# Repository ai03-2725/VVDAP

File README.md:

# VVDAP
Variable voltage isolated DAPLink programmer  

**Warning:** Currently untested.  
If testing, proceed at your own risk.  

## Features
- DAPLink capabilities
  - [DAPLink](https://daplink.io) programming device for flashing Arm Cortex devices
  - Standard 10-pin (5x2) 1.27mm pitch Cortex debug connector for connection to target
  - Exposes UART pins - for future variable-voltage UART module addon via spring-loaded headers
- Variable voltage
  - Variable I/O voltage from 1.8 to 3.6V which self-adjusts to match the target VCC voltage provided on Vtref pin of debug header
- Protection
  - Full isolation between host and target to avoid ground loops or damage to host
  - ESD protection on USB lines and debug connector I/O
  - Polyfuse on USB VBUS
- Modern nice-to-haves
  - USB-C 
  - Fairly compact single-board solution
  - Relatively straightforward to solder at home with a reflow plate and (possibly 3D-printed) solder paste stencil
  - Very affordable (likely <15 USD) compared to the multi-hundred dollar commercial programmers

## Credits
This project builds upon the shoulders of giants - credits go to the following for nearly all of the heavy lifting.  
- [XIVN1987's DAPLink port](https://github.com/XIVN1987/DAPLink) to the CH32V203 microcontroller
- [XIVN1987's reference CH32V203/AT32F425 hardware design](https://oshwhub.com/xivn1987/daplink) for the above port
- [盐汽水-BD4USQ's DAPLink isolator design](https://oshwhub.com/yanqisui/dap-jlink-ge-li-diao-shi-kuo-zhan-ka) (and in turn the projects which it credits) which makes push-pull SWDIO possible over unidirectional isolators/transcievers 

## Changes from the above
- Swapped the digital I/O isolator to an ADuM162N capable of reaching low I/O voltage levels
- Added ESD protection on USB and I/O lines using TPD4E05U06 and ESD5Z5V0 TVS diodes
- Isolated voltage supply rail using the MIE1W0505/R05C1TF05S compact isolated DC/DC converter
- Added a TPS7B4250 tracking LDO to replicate the voltage provided on the Vtref pin of the debug header from the isolated supply rail, which in turn powers the secondary side of the I/O isolator and push-pull splitter
- Changed output connector to a 10-pin (2x5) 1.27mm pitch Cortex debug header
- Removed all power output capabilities 
  - Target should self-power to avoid potentially dangerous voltage mismatches, reverse voltage injection into circuitry not designed to withstand it, or voltage injection into batteries
- Misc component swaps

## Todo
- Produce and test
- Make a 3D printed case
- Make a variable voltage UART module which stacks onto the main board

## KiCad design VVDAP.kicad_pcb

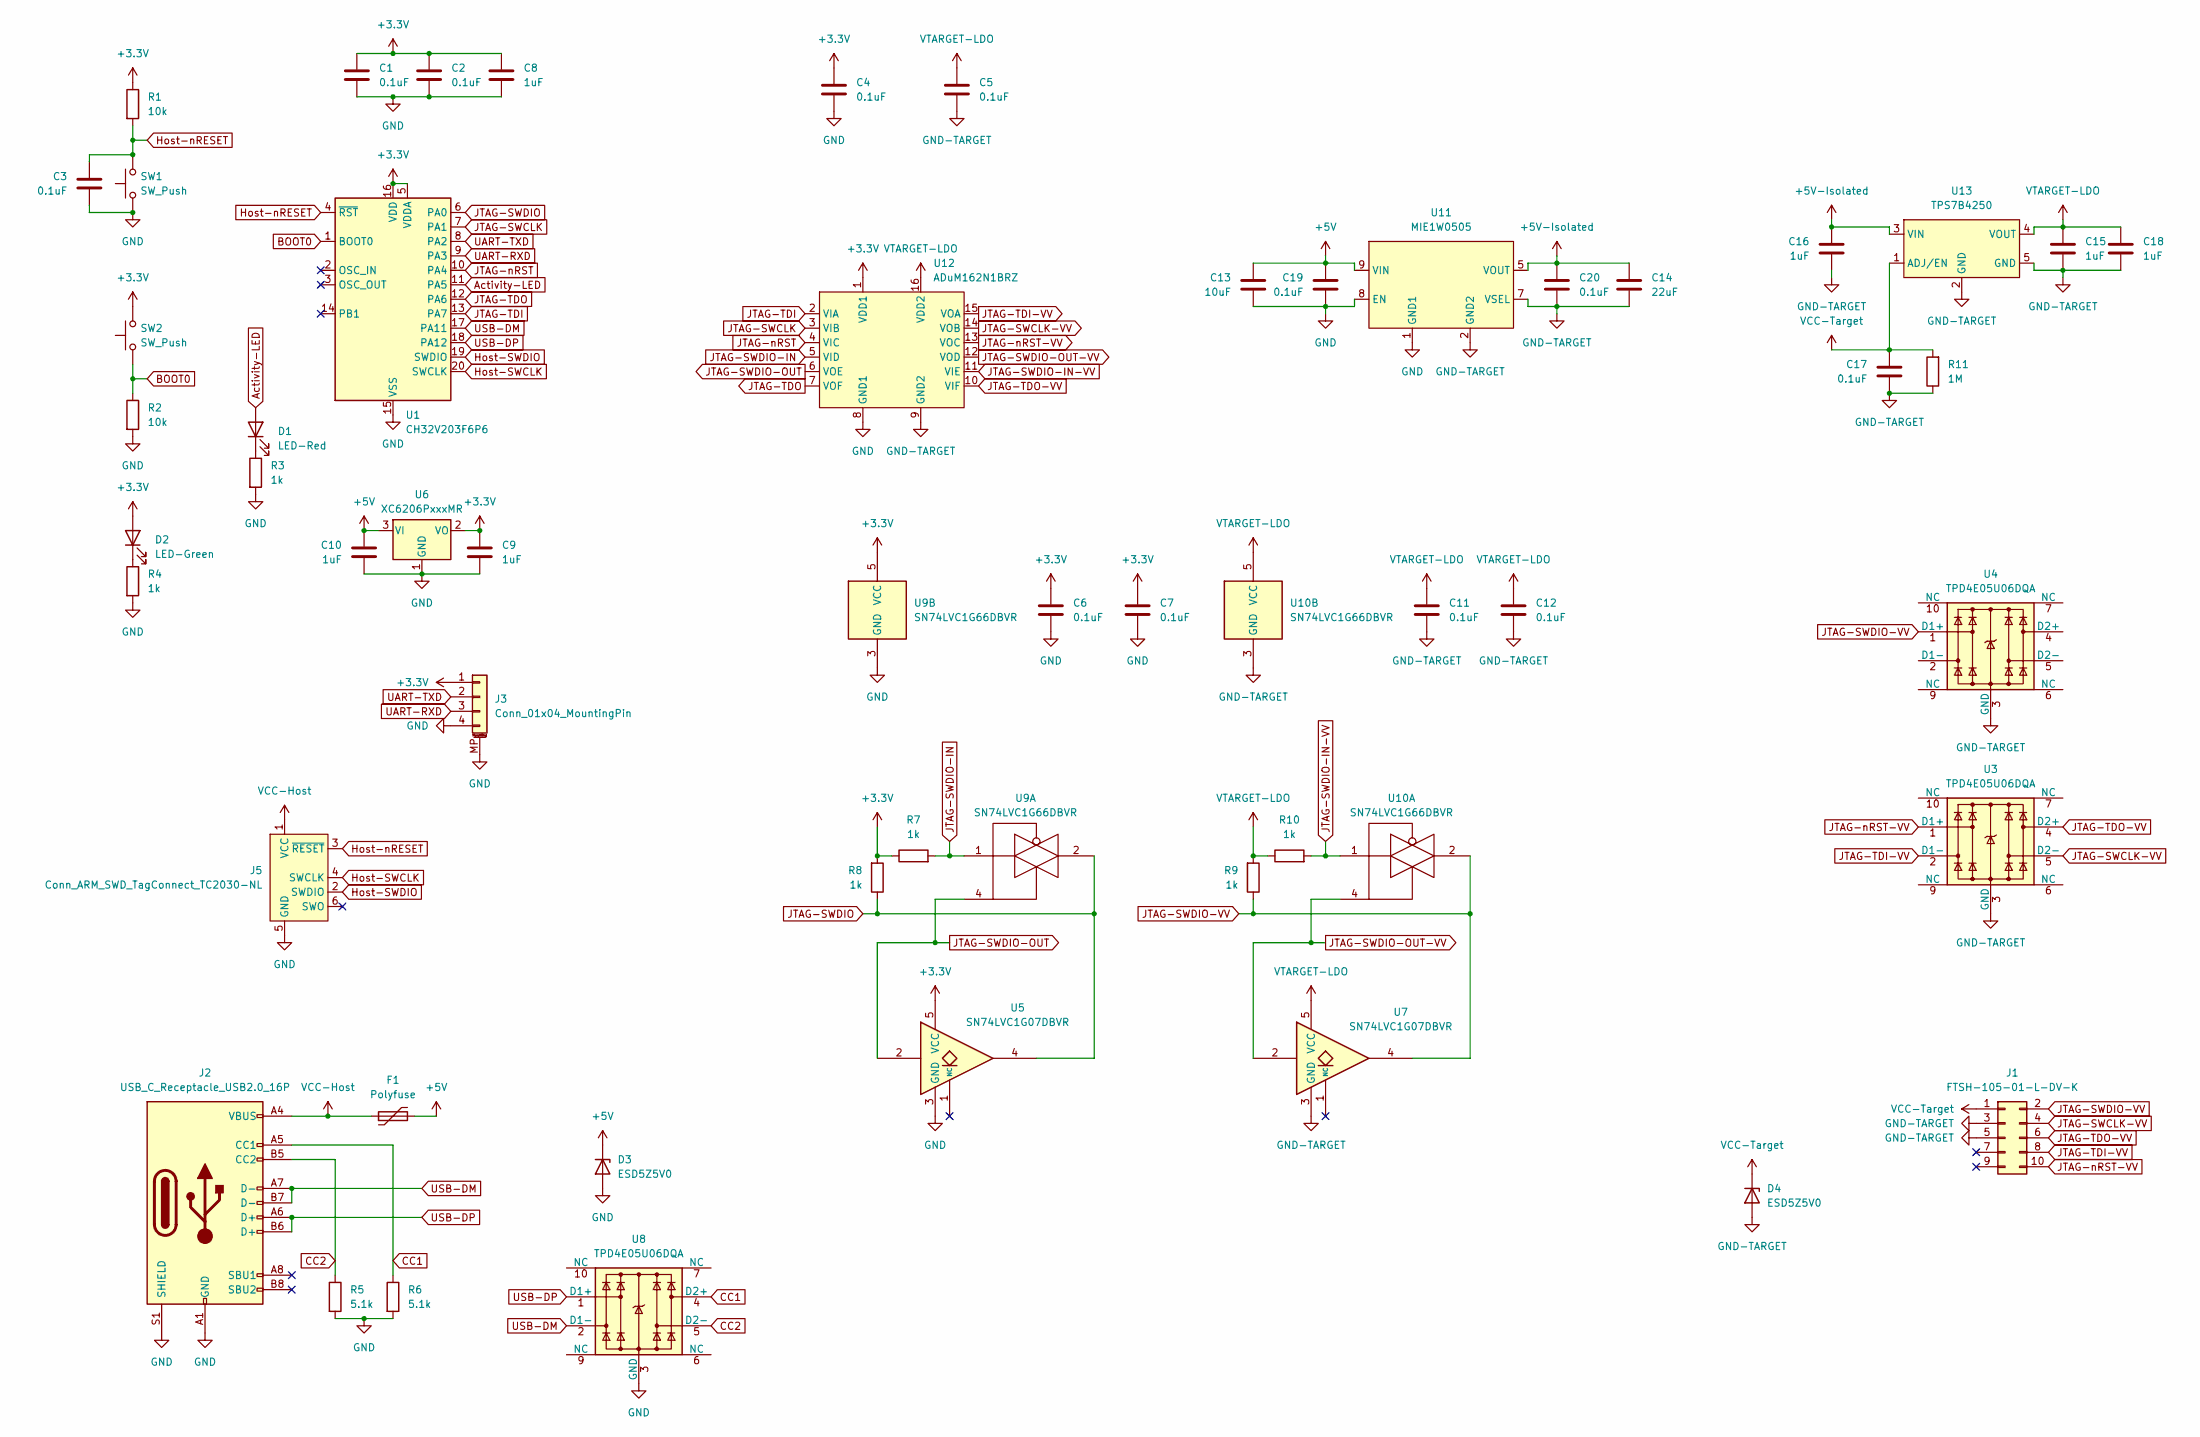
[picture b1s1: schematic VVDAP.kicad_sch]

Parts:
C1, C2, C3, C4, C5, C6, C7, C11, C12, C17, C19, C20: 0.1uF; C_0603_1608Metric
C8, C9, C10, C15, C16, C18: 1uF; C_0603_1608Metric
C13: 10uF; C_0603_1608Metric
C14: 22uF; C_1206_3216Metric
D1: LED-Red; LED_0603_1608Metric
D2: LED-Green; LED_0603_1608Metric
D3, D4: ESD5Z5V0; D_SOD-523
F1: Polyfuse; Fuse_1206_3216Metric
J1: FTSH-105-01-L-DV-K
J2: USB_C_Receptacle_USB2.0_16P; USB_C_Receptacle_HRO_TYPE-C-31-M-12
J3: Conn_01x04_MountingPin; PogoReceiver-2.54-4
J5: Conn_ARM_SWD_TagConnect_TC2030-NL; Tag-Connect_TC2030-IDC-NL_2x03_P1.27mm_Vertical
R1, R2: 10k; R_0603_1608Metric
R3, R4, R7, R8, R9, R10: 1k; R_0603_1608Metric
R5, R6: 5.1k; R_0603_1608Metric
R11: 1M; R_0603_1608Metric
SW1, SW2: SW_Push; SW_SPST_TS-1088-xR020
U1: CH32V203F6P6; TSSOP-20_4.4x6.5mm_P0.65mm
U3, U4, U8: TPD4E05U06DQA; USON-10_2.5x1.0mm_P0.5mm
U5, U7: SN74LVC1G07DBVR; SOT-23-5
U6: XC6206PxxxMR; SOT-23-3
U9, U10: SN74LVC1G66DBVR; SOT-23-5
U11: MIE1W0505
U12: ADuM162N1BRZ; SOIC-16_3.9x9.9mm_P1.27mm
U13: TPS7B4250; SOT-23-5

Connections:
+3.3V: C1.1, C2.1, C4.1, C6.1, C7.1, C8.1, C9.1, D2.2 (A), J3.1, R1.1, R7.1, R8.2, SW2.2, U1.5 (VDDA), U1.16 (VDD), U5.5 (VCC), U6.2 (VO), U9.5 (VCC), U12.1 (VDD1)
+5V: C10.1, C13.1, C19.1, D3.1 (K), F1.2, U6.3 (VI), U11.9 (VIN), U11.10 (VIN)
+5V-Isolated: C14.1, C16.1, C20.1, U11.5 (VOUT), U11.6 (VOUT), U13.3 (VIN)
Activity-LED: D1.2 (A), U1.11 (PA5)
BOOT0: R2.1, SW2.1, U1.1 (BOOT0)
CC1: J2.A5 (CC1), R6.1, U8.4 (D2+)
CC2: J2.B5 (CC2), R5.1, U8.5 (D2-)
GND: C1.2, C2.2, C3.2, C4.2, C6.2, C7.2, C8.2, C9.2, C10.2, C13.2, C19.2, D3.2 (A), J2.A1 (GND), J2.A12 (GND), J2.B1 (GND), J2.B12 (GND), J2.S1 (SHIELD), J3.4, J3.MP (MountPin), J5.5 (GND), R2.2, R3.2, R4.2, R5.2, R6.2, SW1.1, U1.15 (VSS), U5.3 (GND), U6.1 (GND), U8.3 (GND), U8.8 (GND), U9.3 (GND), U11.1 (GND1), U11.8 (EN), U11.11 (GND1), U11.12 (GND1), U12.8 (GND1)
GND-TARGET: C5.2, C11.2, C12.2, C14.2, C15.2, C16.2, C17.2, C18.2, C20.2, D4.2 (A), J1.3, J1.5, R11.1, U3.3 (GND), U3.8 (GND), U4.3 (GND), U4.8 (GND), U7.3 (GND), U10.3 (GND), U11.2 (GND2), U11.3 (GND2), U11.4 (GND2), U11.7 (VSEL), U12.9 (GND2), U13.2 (GND), U13.5 (GND)
Host-SWCLK: J5.4 (SWCLK), U1.20 (SWCLK)
Host-SWDIO: J5.2 (SWDIO), U1.19 (SWDIO)
Host-nRESET: C3.1, J5.3 (~RESET), R1.2, SW1.2, U1.4 (~RST)
JTAG-SWCLK: U1.7 (PA1), U12.3 (VIB)
JTAG-SWCLK-VV: J1.4, U3.5 (D2-), U12.14 (VOB)
JTAG-SWDIO: R8.1, U1.6 (PA0), U5.4, U9.2
JTAG-SWDIO-IN: R7.2, U9.1, U12.5 (VID)
JTAG-SWDIO-IN-VV: R10.2, U10.1, U12.11 (VIE)
JTAG-SWDIO-OUT: U5.2, U9.4, U12.6 (VOE)
JTAG-SWDIO-OUT-VV: U7.2, U10.4, U12.12 (VOD)
JTAG-SWDIO-VV: J1.2, R9.1, U4.1 (D1+), U7.4, U10.2
JTAG-TDI: U1.13 (PA7), U12.2 (VIA)
JTAG-TDI-VV: J1.8, U3.2 (D1-), U12.15 (VOA)
JTAG-TDO: U1.12 (PA6), U12.7 (VOF)
JTAG-TDO-VV: J1.6, U3.4 (D2+), U12.10 (VIF)
JTAG-nRST: U1.10 (PA4), U12.4 (VIC)
JTAG-nRST-VV: J1.10, U3.1 (D1+), U12.13 (VOC)
unnamed: D1.1 (K), R3.1
unnamed: D2.1 (K), R4.1
UART-RXD: J3.3, U1.9 (PA3)
UART-TXD: J3.2, U1.8 (PA2)
USB-DM: J2.A7 (D-), J2.B7 (D-), U1.17 (PA11), U8.2 (D1-)
USB-DP: J2.A6 (D+), J2.B6 (D+), U1.18 (PA12), U8.1 (D1+)
VCC-Host: F1.1, J2.A4 (VBUS), J2.A9 (VBUS), J2.B4 (VBUS), J2.B9 (VBUS), J5.1 (VCC)
VCC-Target: C17.1, D4.1 (K), J1.1, R11.2, U13.1 (ADJ/EN)
VTARGET-LDO: C5.1, C11.1, C12.1, C15.1, C18.1, R9.2, R10.1, U7.5 (VCC), U10.5 (VCC), U12.16 (VDD2), U13.4 (VOUT)

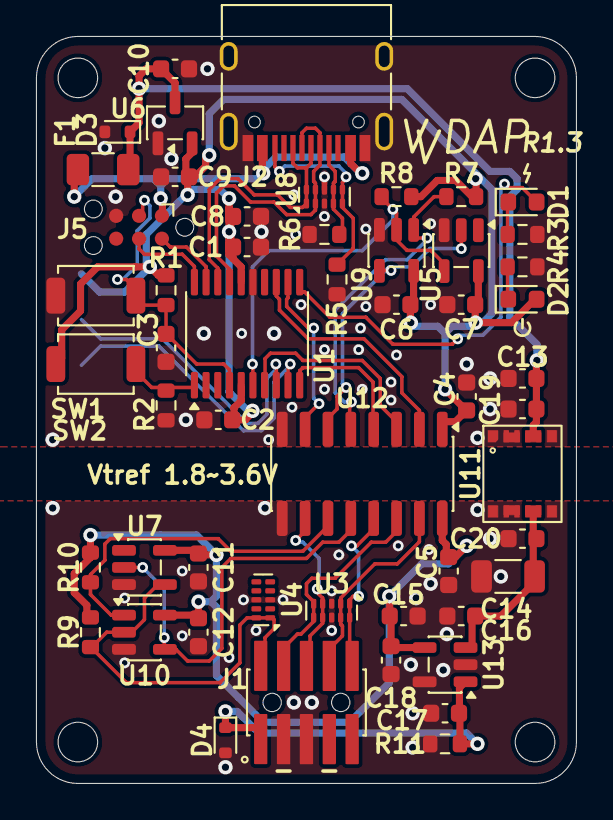
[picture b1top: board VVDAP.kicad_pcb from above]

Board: 2 copper layers, 30.0 x 41.5 mm, 54 parts (1 on the bottom side), 35 nets.

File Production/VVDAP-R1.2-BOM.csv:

Reference,Qty,Value,DNP,Footprint,Description
"C1,C2,C3,C4,C5,C6,C7,C11,C12,C17,C19,C20",12,0.1uF,,Capacitor_SMD:C_0603_1608Metric,"Ceramic capacitor, 0603, X7R, min 10V"
"C8,C9,C10,C15,C16,C18",6,1uF,,Capacitor_SMD:C_0603_1608Metric,"Ceramic capacitor, 0603, X7R, min 10V"
C13,1,10uF,,Capacitor_SMD:C_0603_1608Metric,"Ceramic capacitor, 0603, X7R, min 10V"
C14,1,22uF,,Capacitor_SMD:C_1206_3216Metric,"Ceramic capacitor, 1206, X7R, min 10V"
D1,1,LED-Red,,LED_SMD:LED_0603_1608Metric,"Light emitting diode, 0603, Red"
D2,1,LED-Green,,LED_SMD:LED_0603_1608Metric,"Light emitting diode, 0603, Green"
"D3,D4",2,ESD5Z5V0,,Diode_SMD:D_SOD-523,"ESD Protection Diode, SOD-523"
F1,1,Polyfuse,,Fuse:Fuse_1206_3216Metric,"Resettable PTC fuse, 1A hold, 10V min"
J1,1,FTSH-105-01-L-DV-K,,locallib:FTSH-105-01-L-DV-K,FTSH-105-01-L-DV-K 1.27mm pitch 2x5 pin connector
J2,1,USB_C_Receptacle_USB2.0_16P,,Connector_USB:USB_C_Receptacle_HRO_TYPE-C-31-M-12,HRO TYPE-C-31-M-12 USB Type-C Receptacle connector
"R1,R2",2,10k,,Resistor_SMD:R_0603_1608Metric,"Resistor, 0603"
"R3,R4,R7,R8,R9,R10",6,1k,,Resistor_SMD:R_0603_1608Metric,"Resistor, 0603"
"R5,R6",2,5.1k,,Resistor_SMD:R_0603_1608Metric,"Resistor, 0603"
R11,1,1M,,Resistor_SMD:R_0603_1608Metric,"Resistor, 0603"
"SW1,SW2",2,SW_Push,,Button_Switch_SMD:SW_SPST_TS-1088-xR020,TS-1088 family 3x4mm pushbuttons
U1,1,CH32V203F6P6,,Package_SO:TSSOP-20_4.4x6.5mm_P0.65mm,CH32V203F6P6 Microcontroller
"U3,U4,U8",3,TPD4E05U06DQA,,Package_SON:USON-10_2.5x1.0mm_P0.5mm,"4-Channel ESD Protection for Super-Speed USB 3.0 Interface, USON-10"
"U5,U7",2,SN74LVC1G07DBVR,,Package_TO_SOT_SMD:SOT-23-5,"Single Buffer Gate, Open Drain, Low-Voltage CMOS"
U6,1,XC6206P332MR,,Package_TO_SOT_SMD:SOT-23-3,"Positive 60-250mA Low Dropout Regulator, Fixed Output, SOT-23"
"U9,U10",2,SN74LVC1G66DBVR,,Package_TO_SOT_SMD:SOT-23-5,"Single Bilateral Analog Switch, SOT-23-5/SC-70-5"
U11,1,MIE1W0505,,locallib:MIE1W0505,"Thin 4x5mm isolated DC-DC module with symmetrical pads - MIE1W0505, R05C1TF05S, and equivalents"
U12,1,ADuM162N1BRZ,,Package_SO:SOIC-16_3.9x9.9mm_P1.27mm,ADuM162N1BRZ digital I/O isolator
U13,1,TPS7B4250,,Package_TO_SOT_SMD:SOT-23-5,TPS7B4250 tracking LDO
,,,,,
Total,52,,,,

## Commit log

2026-01-06 Update renders; adjust edge cuts slightly
2026-01-06 Update screw pads
2026-01-06 Revert outline to G1 due to visual issues
